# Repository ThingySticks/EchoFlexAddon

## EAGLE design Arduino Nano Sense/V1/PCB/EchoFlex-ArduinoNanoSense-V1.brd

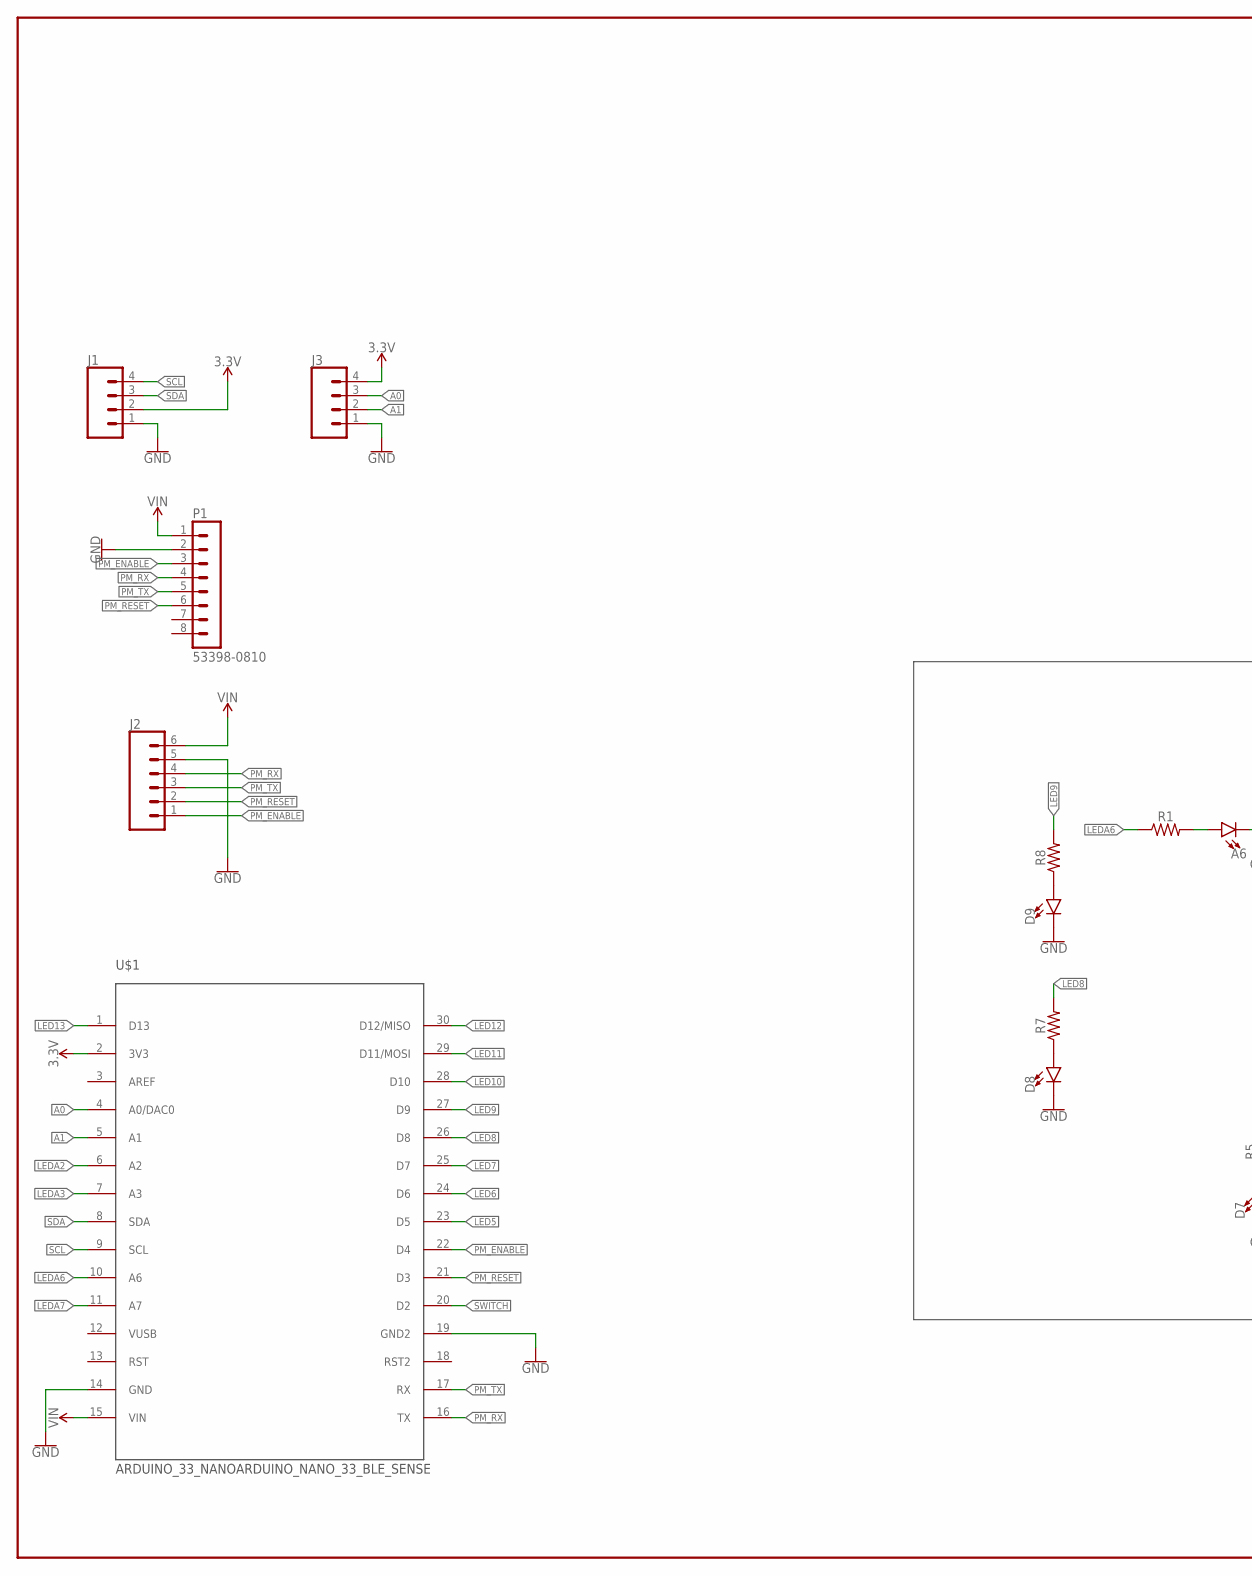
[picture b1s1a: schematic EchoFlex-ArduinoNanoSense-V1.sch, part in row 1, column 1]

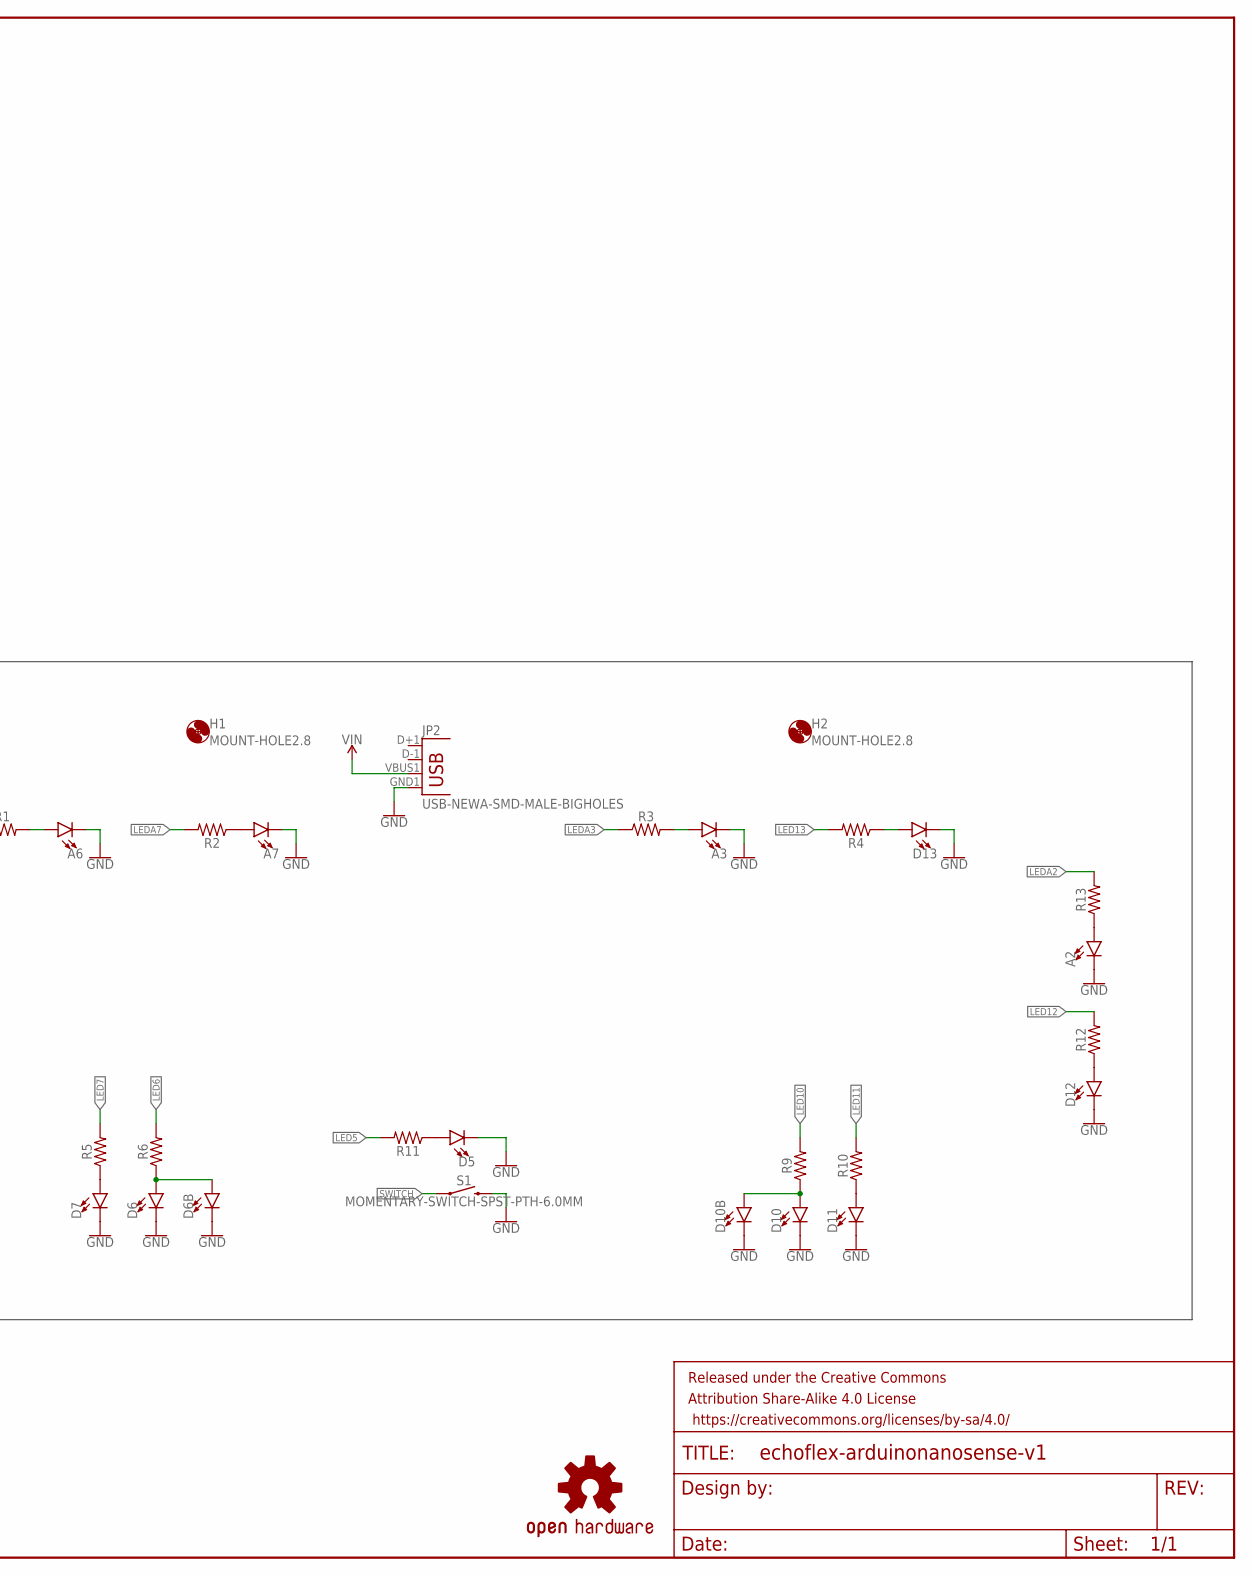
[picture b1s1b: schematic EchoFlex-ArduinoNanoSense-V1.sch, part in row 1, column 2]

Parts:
A2, A3, A6, A7: LED1206; LED-1206
D5, D6, D6B, D7, D8, D9, D10, D10B, D11, D12, D13: LED1206; LED-1206
FRAME1: FRAME-LEDGER; CREATIVE_COMMONS
H1, H2: MOUNT-HOLE2.8; 2,8
J1: CONN_04SMD2; JST04_1MM_RA
J2: CONN_06SILK_FEMALE_PTH; 1X06
J3: CONN_04; 1X04
JP2: USB-NEWA-SMD-MALE-BIGHOLES; USB-A-SMT-MALE
LOGO1: OSHW-LOGOM; OSHW-LOGO-M
P1: 53398-0810
R1, R2, R3, R4, R5, R6, R7, R8, R9, R10, R11, R12, R13: 0805
S1: MOMENTARY-SWITCH-SPST-PTH-6.0MM; TACTILE_SWITCH_PTH_6.0MM
U$1: ARDUINO_33_NANOARDUINO_NANO_33_BLE_SENSE; ARDUINO_NANO_33

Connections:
3.3V: J1.2, J3.4, U$1.2 (3V3)
A0: J3.3, U$1.4 (A0/DAC0)
A1: J3.2, U$1.5 (A1)
GND: A2.C, A3.C, A6.C, A7.C, D5.C, D6.C, D6B.C, D7.C, D8.C, D9.C, D10.C, D10B.C, D11.C, D12.C, D13.C, J1.1, J2.5, J3.1, JP2.GND1 (GND), P1.2, S1.3 (2), U$1.14 (GND), U$1.19 (GND2)
LED5: R11.2, U$1.23 (D5)
LED6: R6.2, U$1.24 (D6)
LED7: R5.2, U$1.25 (D7)
LED8: R7.2, U$1.26 (D8)
LED9: R8.2, U$1.27 (D9)
LED10: R9.2, U$1.28 (D10)
LED11: R10.2, U$1.29 (D11/MOSI)
LED12: R12.2, U$1.30 (D12/MISO)
LED13: R4.2, U$1.1 (D13)
LEDA2: R13.2, U$1.6 (A2)
LEDA3: R3.1, U$1.7 (A3)
LEDA6: R1.1, U$1.10 (A6)
LEDA7: R2.2, U$1.11 (A7)
unnamed: D12.A, R12.1
unnamed: D7.A, R5.1
unnamed: D6.A, D6B.A, R6.1
unnamed: D8.A, R7.1
unnamed: A6.A, R1.2
unnamed: A7.A, R2.1
unnamed: A3.A, R3.2
unnamed: D13.A, R4.1
unnamed: D9.A, R8.1
unnamed: D10.A, D10B.A, R9.1
unnamed: D11.A, R10.1
unnamed: D5.A, R11.1
unnamed: A2.A, R13.1
PM_ENABLE: J2.1, P1.3, U$1.22 (D4)
PM_RESET: J2.2, P1.6, U$1.21 (D3)
PM_RX: J2.4, P1.4, U$1.16 (TX)
PM_TX: J2.3, P1.5, U$1.17 (RX)
SCL: J1.4, U$1.9 (SCL)
SDA: J1.3, U$1.8 (SDA)
SWITCH: S1.1, U$1.20 (D2)
VIN: J2.6, JP2.VBUS1 (VBUS), P1.1, U$1.15 (VIN)
VUSB: U$1.12 (VUSB)

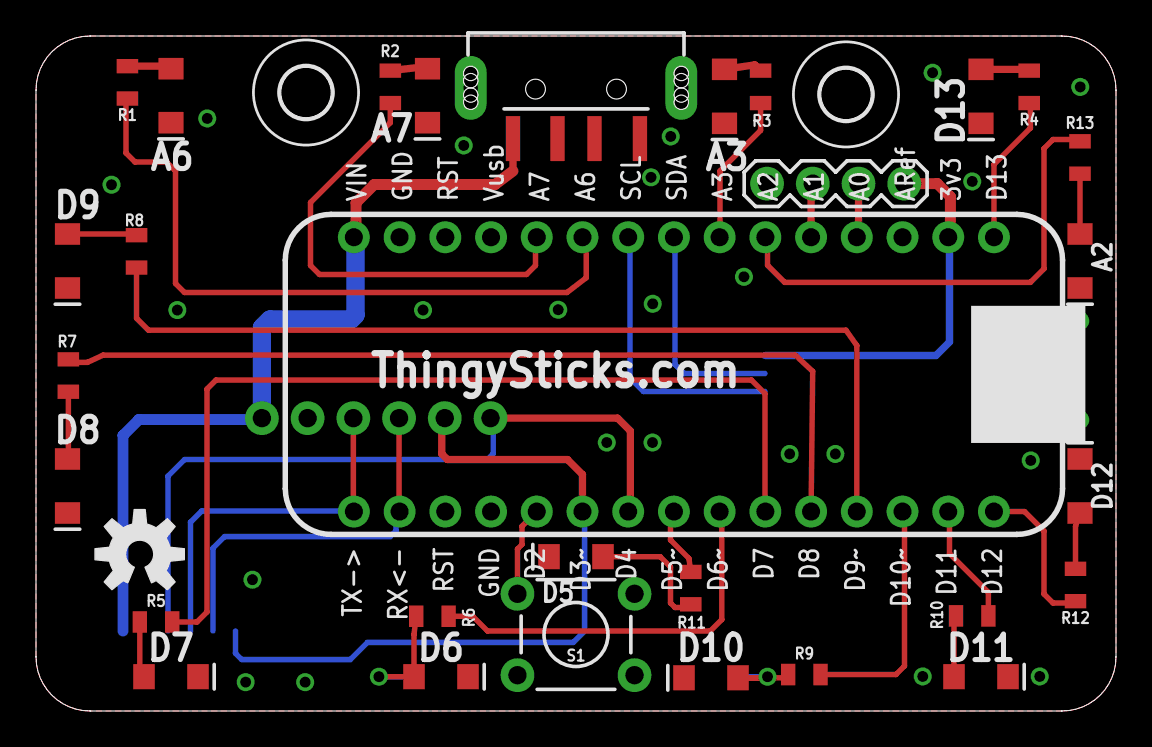
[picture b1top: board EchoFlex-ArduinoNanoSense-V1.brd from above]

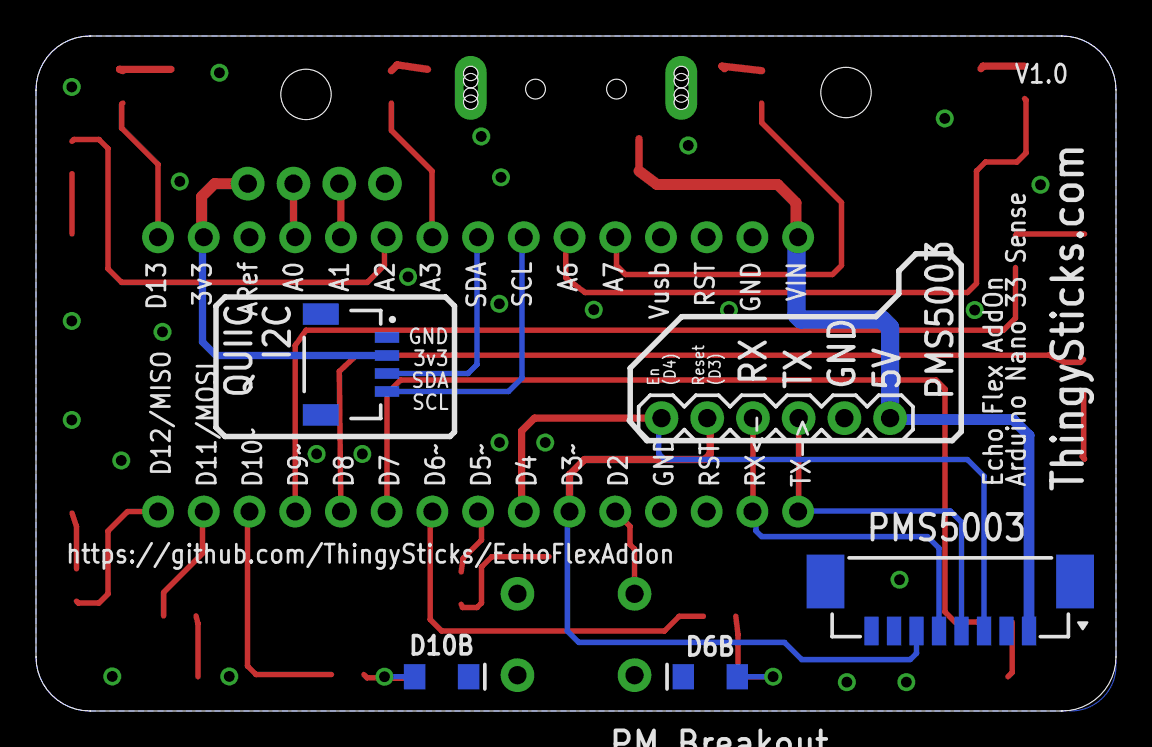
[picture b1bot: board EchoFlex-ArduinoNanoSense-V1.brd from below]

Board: 2 copper layers, 60.0 x 37.5 mm, 39 parts (5 on the bottom side), 38 nets.

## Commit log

2020-01-19 Initial version
2020-01-19 Added text, fixed outline.

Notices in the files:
parts and their libraries:
SparkFun-Aesthetics: Licensing: Creative Commons ShareAlike 4.0 International - https://creativecommons.org/licenses/by-sa/4.0
SparkFun-Aesthetics: Released under the Creative Commons Attribution Share-Alike 4.0 License
SparkFun-Aesthetics: https://creativecommons.org/licenses/by-sa/4.0
